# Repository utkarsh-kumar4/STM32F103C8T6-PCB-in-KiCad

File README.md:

<h1 align="center">⚙️ STM32F103C8T6 Custom PCB in Kicad</h1>

<h2>📘 Overview</h2>
<p>
This project presents a fully designed and routed PCB based on the <b>STM32F103C8T6</b> microcontroller — a popular ARM Cortex-M3 based MCU used widely in embedded systems, control units, and IoT applications. 
The design covers schematic creation, PCB layout, 3D rendering, and Gerber file generation using <b>KiCad 9.0.4</b>. 
The board integrates essential power regulation, programming/debugging headers, and communication interfaces, making it suitable for both learning and prototyping environments.
</p>

<hr>

<h2>🧩 Features</h2>
<ul>
  <li>Microcontroller: <b>STM32F103C8T6</b> (ARM Cortex-M3, 72 MHz, 64 KB Flash)</li>
  <li>Interfaces: UART, I2C, USB, and SWD Debug</li>
  <li>16 MHz Crystal Oscillator for stable system clock</li>
  <li>AMS1117-3.3V linear regulator from USB VBUS (5V to 3.3V)</li>
  <li>On-board BOOT0 switch for flash and system memory booting</li>
  <li>Compact double-layer PCB with decoupling and bulk capacitors</li>
  <li>All standard headers exposed for breadboard-friendly prototyping</li>
</ul>

<hr>

<h2>🔧 Circuit Design Details</h2>

<h3>Microcontroller Section</h3>
<p>
The core of the design revolves around the <b>STM32F103C8T6</b>. Proper pin mapping and peripheral allocation were done using <b>STM32CubeIDE</b> before schematic creation in KiCad. 
The nomenclature follows standard STM32 conventions:
<ul>
  <li><b>VDD / VDDA</b>: 3.3V supply</li>
  <li><b>VSS / VSSA</b>: Ground reference</li>
  <li><b>VBAT</b>: Backup domain supply (optional in this design)</li>
</ul>
</p>

<h3>Power Supply</h3>
<p>
Power is supplied via the USB connector. The <b>AMS1117-3.3V regulator</b> converts 5V (VBUS) to 3.3V for the MCU and peripherals. 
A combination of <b>decoupling capacitors (100nF per VDD pin)</b> and a <b>bulk capacitor (22µF)</b> ensures voltage stability. 
A <b>ferrite bead (FB1)</b> is used for VDDA filtering to isolate analog noise.
</p>

<h3>Clock Circuit</h3>
<p>
A <b>16 MHz crystal oscillator</b> (Y1) provides the external clock source. Load capacitors (C12, C13) are calculated based on crystal datasheet using:
<code>CL = 2 × (C_L - C_stray)</code>. 
The crystal’s ground pads are tied to <b>Crystal_GND24</b> for EMI reduction.
</p>

<h3>Reset and Boot Configuration</h3>
<p>
The <b>NRST</b> pin is connected to a pull-up resistor and reset header, allowing manual or external resets. 
A <b>BOOT0 switch</b> lets users toggle between Flash memory boot and system memory boot modes for easy firmware flashing.
</p>

<h3>USB Interface</h3>
<p>
The <b>Micro USB Type-B connector</b> provides both power and data interface. 
Differential data lines (<b>USB_D+</b> and <b>USB_D−</b>) are routed as a <b>differential pair</b> in KiCad for signal integrity. 
The <b>VBUS</b> pin powers the regulator, and <b>USB shield</b> is tied to board ground through high-value resistance to reduce noise coupling.
</p>

<h3>Communication Interfaces</h3>
<p>
The board exposes the following interfaces:
<ul>
  <li><b>UART</b> – USART1_TX, USART1_RX for serial communication</li>
  <li><b>I2C</b> – I2C1_SCL, I2C1_SDA for sensor and peripheral interfacing</li>
  <li><b>SWD</b> – Serial Wire Debug (PA13, PA14) for programming and debugging</li>
</ul>
These headers simplify firmware upload and real-time debugging using ST-Link or similar tools.
</p>

<hr>

<h2>💻 KiCad Project Workflow</h2>
<p>
The PCB was designed in <b>KiCad</b> following standard embedded design practices. ERC (Electrical Rules Check) and DRC (Design Rules Check) were performed to ensure design integrity before Gerber generation.
</p>

<ul>
  <li><b>ERC:</b> Validates schematic-level connections and symbol consistency.</li>
  <li><b>DRC:</b> Checks trace clearances, copper spacing, and via placements.</li>
  <li><b>Gerber Files:</b> Generated for manufacturing and fabrication verification.</li>
</ul>

<hr>

<h2>🧠 Learnings</h2>
<p>
This project helped reinforce key embedded hardware design concepts:
<ul>
  <li>Understanding STM32 power domains (VDD, VDDA, VBAT)</li>
  <li>Implementing decoupling and bulk capacitors for stable operation</li>
  <li>Applying ferrite beads for analog noise isolation</li>
  <li>Routing differential USB pairs in KiCad</li>
  <li>Debugging using SWD and BOOT0 configuration</li>
  <li>Generating and verifying ERC/DRC-compliant Gerber files</li>
</ul>
It also provided insight into the workflow of transforming a schematic into a professional-grade PCB suitable for embedded applications.
</p>

<hr>

<h2>📷 Project Images</h2>
<h3>🔹 Schematic Design</h3>

<h3>🔹 PCB Layout</h3>

<h3>🔹 3D Board View</h3>

## Author 👤
[Utkarsh Kumar](https://github.com/utkarsh-kumar4) 👨🏻‍💻🎓

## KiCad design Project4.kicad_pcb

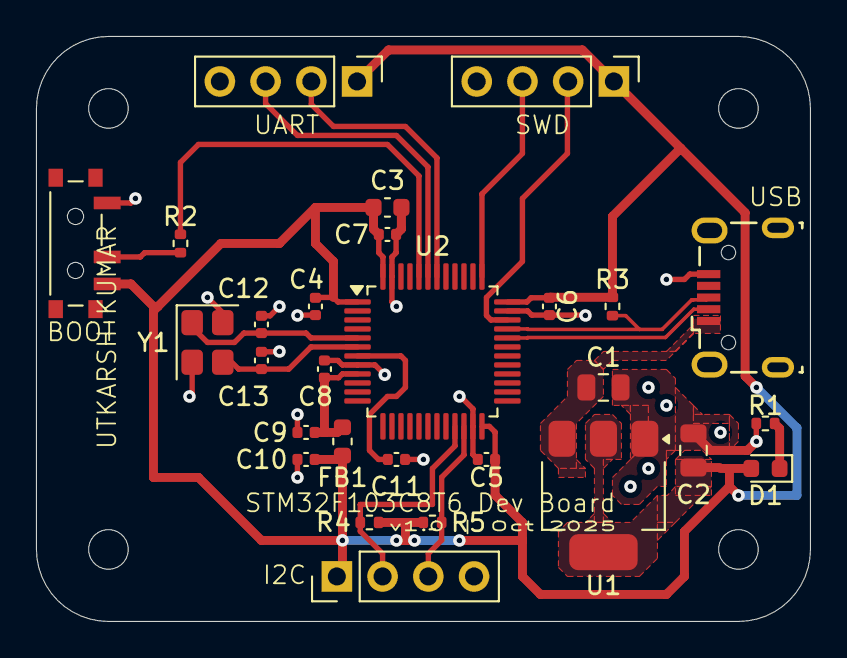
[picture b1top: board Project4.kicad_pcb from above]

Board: 2 copper layers, 43.0 x 32.5 mm, 32 parts (0 on the bottom side), 18 nets.

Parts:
C1, C2: 22u; C_0805_2012Metric
C3: 10u; C_0603_1608Metric
C4, C5, C6, C7, C11: 100n; C_0402_1005Metric
C8: 10n; C_0402_1005Metric
C9, C10: 1u; C_0402_1005Metric
C12, C13: 10p; C_0402_1005Metric
D1: RED; LED_0603_1608Metric
FB1: 120R; L_0603_1608Metric
H1, H2, H3, H4: MountingHole; MountingHole_2.2mm_M2
J1: USB_B_Micro; USB_Micro-B_Wuerth_629105150521
J2, J3, J4: Conn_01x04_Pin; PinHeader_1x04_P2.54mm_Vertical
R1, R3, R4, R5: 1.5k; R_0402_1005Metric
R2: 10k; R_0402_1005Metric
SW1: SW_SPDT; SW_SPDT_PCM12
U1: AMS1117-3.3; SOT-223-3_TabPin2
U2: STM32F103C8T6; LQFP-48_7x7mm_P0.5mm
Y1: 16MHz; Crystal_SMD_3225-4Pin_3.2x2.5mm

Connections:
+3.3V: C2.1, C3.1, C4.1, C5.1, C6.1, C7.1, C10.1, D1.2 (A), FB1.2, J2.1, J3.1, J4.1, R3.1, R4.1, R5.1, SW1.3 (C), U1.2 (VO), U2.1 (VBAT), U2.24 (VDD), U2.36 (VDD), U2.48 (VDD)
+3.3VA: C8.1, C9.1, FB1.1, U2.9 (VDDA)
/BOOT0: R2.1, U2.44 (BOOT0)
/HSE_IN: C12.1, U2.5 (PD0), Y1.1
/HSE_OUT: C13.1, U2.6 (PD1), Y1.3
/I2C2_SCL: J4.2, R4.2, U2.21 (PB10)
/I2C2_SDA: J4.3, R5.2, U2.22 (PB11)
/NRST: C11.1, U2.7 (NRST)
/PWR_LED_K: D1.1 (K), R1.1
/SWCLK: J3.3, U2.37 (PA14)
/SWDIO: J3.2, U2.34 (PA13)
/SW_BOOT0: R2.2, SW1.2 (B)
/USART1_RX: J2.3, U2.43 (PB7)
/USART1_TX: J2.2, U2.42 (PB6)
/USB_D+: J1.3 (D+), R3.2, U2.33 (PA12)
/USB_D-: J1.2 (D-), U2.32 (PA11)
GND: C1.2, C2.2, C3.2, C4.2, C5.2, C6.2, C7.2, C8.2, C9.2, C10.2, C11.2, C12.2, C13.2, J1.5 (GND), J2.4, J3.4, J4.4, R1.2, SW1.1 (A), U1.1 (GND), U2.8 (VSSA), U2.23 (VSS), U2.35 (VSS), U2.47 (VSS), Y1.2, Y1.4
VBUS: C1.1, J1.1 (VBUS), U1.3 (VI)
